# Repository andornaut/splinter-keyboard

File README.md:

# Splinter keyboard

A 62-key split columnar ergonomic keyboard.

**Status:** v4 PCB and case built and confirmed working with the [Splinter firmware](https://github.com/andornaut/qmk_firmware/tree/splinter/keyboards/splinter).

This repo holds the hardware design files; firmware lives in a [separate repo](https://github.com/andornaut/qmk_firmware/tree/splinter/keyboards/splinter). Design pipeline: Keyboard Layout Editor -> Ergogen -> KiCad -> fabrication -> Onshape -> OrcaSlicer -> QMK (see [Developing](#developing)).

Related notes: [3D printing](https://github.com/andornaut/til/blob/main/docs/3d-printing.md), [electronics](https://github.com/andornaut/til/blob/main/docs/electronics.md), [keyboards](https://github.com/andornaut/til/blob/main/docs/keyboards.md).

## Versions

| Version    | MCU                                                                                                        | Changes from previous                                              | Firmware                                                                                         | Photo                                      |
| ---------- | ---------------------------------------------------------------------------------------------------------- | ------------------------------------------------------------------ | ------------------------------------------------------------------------------------------------ | ------------------------------------------ |
| [v4](./v4) | [splitkb Liatris](https://splitkb.com/products/liatris) (RP2040)                                           | Added USB VBUS detection and TRRS ESD protection                   | [splinter](https://github.com/andornaut/qmk_firmware/tree/splinter/keyboards/splinter)           | Pending                                    |
| [v3](./v3) | [Adafruit KB2040](https://www.adafruit.com/product/5302) (RP2040)                                          | Switched from AVR to RP2040                                        | [splinter-v3.0](https://github.com/andornaut/qmk_firmware/tree/splinter-v3.0/keyboards/splinter) |  |
| [v2](./v2) | [SparkFun Pro Micro](https://www.sparkfun.com/sparkfun-qwiic-pro-micro-usb-c-atmega32u4.html) (ATmega32U4) | Symmetrical enclosures; added a key (62 keys)                      | [splinter-2.0](https://github.com/andornaut/qmk_firmware/tree/splinter-2.0/keyboards/splinter)   |  |
| [v1](./v1) | [SparkFun Pro Micro](https://www.sparkfun.com/sparkfun-qwiic-pro-micro-usb-c-atmega32u4.html) (ATmega32U4) | Initial version: 61 keys, columnar layout, asymmetrical enclosures | [splinter-1.0](https://github.com/andornaut/qmk_firmware/tree/splinter-1.0/keyboards/splinter)   |  |

## Repository layout

Every version directory (`v1/` .. `v4/`) follows the same shape, though not every version has every part:

| Path                      | Contents                                                                                                                                                             |
| ------------------------- | -------------------------------------------------------------------------------------------------------------------------------------------------------------------- |
| `ergogen/config.yaml`     | Keyboard definition. The source of truth for everything downstream.                                                                                                  |
| `ergogen/footprints/`     | Symlink to the shared footprints below, so every version builds against one pinned set. Do not edit.                                                                 |
| `keyboard-layout-editor/` | Layout prototypes.                                                                                                                                                   |
| `kicad/unrouted/`         | Working boards. Ergogen generates into these; you route here.                                                                                                        |
| `kicad/routed/`           | Routed masters. The fab source.                                                                                                                                      |
| `kicad/unrouted-backups/` | Timestamped copies of the `unrouted/` boards, taken each time fresh ones overwrite them. Gitignored, and only the last few per board are kept.                       |
| `kicad/jlcpcb-parts.json` | LCSC part numbers, kept outside the `.kicad_pcb` so they survive regeneration. v4 only, and what makes assembly files appear.                                        |
| `onshape/`                | Case design and its exported STEP. v4 adds the build sheet, the rationale, and a script that builds the same design as geometry and validates the export against it. |
| `orcaslicer/`             | Slicer projects. v2 and v3 only.                                                                                                                                     |

Shared across versions:

| Path       | Contents                                |
| ---------- | --------------------------------------- |
| `ergogen/` | Footprints and helpers.                 |
| `scripts/` | Build steps.                            |
| `dist/`    | Build output. Generated, not committed. |

A `_` prefix on a PCB filename excludes it from every step.

## Installation

| Tool                                                      | Needed for                                                                                     |
| --------------------------------------------------------- | ---------------------------------------------------------------------------------------------- |
| [KiCad 10](https://www.kicad.org)                         | Routing, and `kicad-cli` for gerber export and headless DRC                                    |
| [Node.js](https://nodejs.org/en)                          | Ergogen and the npm scripts                                                                    |
| [Python 3](https://www.python.org)                        | The build steps (stdlib only; `pcbnew` comes from KiCad)                                       |
| [OrcaSlicer](https://github.com/OrcaSlicer/OrcaSlicer)    | Slicing the printed case                                                                       |
| [FreeCAD](https://www.freecad.org)                        | `freecadcmd`, for [validating the case export](#step-6-onshape)                                |
| [Freerouting](https://github.com/freerouting/freerouting) | Optional, for [autorouting](#autorouting-optional)                                             |
| [KiKit](https://github.com/yaqwsx/KiKit)                  | Optional, for [panelization](#panelization-optional-for-pcba-cost); needs the git-master build |

```bash
# Include submodules when cloning
git clone --recursive git@github.com:andornaut/splinter-keyboard.git
cd splinter-keyboard

# Install the Node version from .nvmrc, then the deps (including Ergogen)
nvm install
npm install

# Install KiCad 10 (provides kicad-cli, used for fab file generation)
sudo add-apt-repository ppa:kicad/kicad-10.0-releases
sudo apt install kicad

# Fallback only if you cloned without --recursive
git submodule update --init --recursive
```

OrcaSlicer, FreeCAD, KiCad, Freerouting and KiKit also install from [these Ansible tasks](https://github.com/andornaut/ansible-ctrl/blob/main/roles/hobbies/tasks/main.yml) (tags `orcaslicer`, `freecad` and `kicad`; Freerouting and KiKit come with `kicad`).

**Updating footprint submodules.** `npm run ergogen` uses `ceoloide` and `infused-kim` at their pinned revision and never advances them, so builds stay reproducible. To re-pin:

```bash
git submodule update --remote ergogen/footprints/ceoloide ergogen/footprints/infused-kim
git add ergogen/footprints/ceoloide ergogen/footprints/infused-kim
git commit -m "Bump footprint submodules"
```

## Commands

Run everything through `npm run` from the repo root: the scripts read the active version from `config.VERSION` in [`package.json`](./package.json).

| Command                                                                            | Does                                                                                       |
| ---------------------------------------------------------------------------------- | ------------------------------------------------------------------------------------------ |
| `pipeline`                                                                         | The full build, every gate in order. The normal entry point. Add `-- -v` for the full log. |
| `ergogen`                                                                          | Generate outlines and PCBs into `dist/${VERSION}/ergogen/`                                 |
| `watch` / `watch:sync-unrouted`                                                    | Re-run `ergogen` on every `config.yaml` change, the second also copying into `unrouted/`   |
| `copy:dist-to-unrouted`                                                            | `dist/` -> `unrouted/` (backs the old boards up to `unrouted-backups/` first)              |
| `copy:traces-to-unrouted`                                                          | Traces and teardrops from `routed/` back into `unrouted/`                                  |
| `copy:unrouted-to-routed`                                                          | `unrouted/` -> `routed/` (see [Saving to routed/](#saving-to-routed))                      |
| `fab`                                                                              | Gerbers, drill, and assembly BOM/CPL via `kicad-cli`                                       |
| `panelize`                                                                         | Combine both halves into one JLCPCB panel (optional)                                       |
| `route`                                                                            | Autoroute `unrouted/` via Freerouting (optional)                                           |
| `validate:provenance` / `validate:symmetry` / `validate:firmware` / `validate:fab` | The four gates (see [Validation](#validation))                                             |
| `clean`                                                                            | Remove `dist/`                                                                             |
| `lint` / `format`                                                                  | Prettier and ESLint, checking or fixing. `lint` is a CI gate                               |

## Developing

### Step 1. Configure

Set `config.VERSION` in [`package.json`](./package.json) to `v1`, `v2`, `v3`, or `v4`, by editing the file or with `npm pkg set config.VERSION=v4`.

### Step 2. [Keyboard Layout Editor](https://www.keyboard-layout-editor.com/)

Prototype a layout, export it to [`keyboard-layout-editor.json`](./v4/keyboard-layout-editor/keyboard-layout-editor.json) so you can re-import and iterate, then use it as the basis for the Ergogen design. To load it into the **Raw data** tab, paste it without its outer `[` and `]`: the tab takes the layout's rows directly, while the downloaded JSON wraps them in an array.

### Step 3. [Ergogen](https://github.com/ergogen/ergogen)

1. `docker compose up` starts the Ergogen GUI (it builds on first run); open <http://ergogen.internal> (needs [docker_etc_hosts](https://github.com/andornaut/docker_etc_hosts) for the `/etc/hosts` entry).
1. Paste in, edit, then download [`ergogen/config.yaml`](./v4/ergogen/config.yaml).
1. `npm run ergogen`, then `npm run copy:dist-to-unrouted`. Or just `npm run watch:sync-unrouted`.

- The GUI renders no PCBs and is client-side only. Edit there, copy back to `config.yaml` (the source of truth), build with `npm run ergogen`.
- The browser cannot load footprints from disk, so the [`Dockerfile`](./Dockerfile) bakes this repo's [custom footprints](./ergogen/footprints/) into the GUI image. An unregistered `what:` shows up as unknown; after adding one, `docker compose build --no-cache`.

### Step 4. [KiCad](https://www.kicad.org/)

Open a board from [`kicad/unrouted/`](./v4/kicad/unrouted/) and route it. Before saving:

- **Add teardrops** (Edit > Edit Teardrops, nothing selected for board-wide): stronger pad and via joints. Re-run after any reroute.
- **Run DRC** (Inspect > Design Rules Checker, "Refill all zones" checked): clear every violation and unrouted net. `npm run fab` re-runs it headlessly, but fixing it here beats reading the JSON.
- **Check copper and silk** visually: no isolated GND islands or stranded pads; silk clear of pads and the board edge.

After regenerating with Ergogen, `npm run copy:traces-to-unrouted` brings the traces and teardrops from `routed/` back into `unrouted/` (then File > Revert in KiCad).

#### Saving to routed/

`npm run copy:unrouted-to-routed` writes the masters' `.kicad_pro` and `.kicad_dru` first, since the stages that move copper measure against the clearances those hold. Then, one master at a time, it copies the working board onto its master in [`kicad/routed/`](./v4/kicad/routed/) and runs:

| Stage        | What it does                                                                                                                 |
| ------------ | ---------------------------------------------------------------------------------------------------------------------------- |
| GND pour     | Floods a ground plane on whichever side costs less (scored per board, F.Cu vs B.Cu)                                          |
| Cleanup      | Strips copper no route uses: dangling tracks and the vias they strand, tracks buried in pads, redundant vias, split segments |
| Pattern snap | Pulls strays onto the repeated shape they belong to, within a per-endpoint cap                                               |
| Sliver tidy  | Collapses any segment left shorter than it is wide, within a per-endpoint cap                                                |

One master at a time, copy included, because any stage can stop the build: a master this run has not reached yet is still the routed board it was, rather than an un-poured working copy that nothing downstream would catch.

The last three stages feed each other: a collapsed sliver can leave a run the next snap recognises, and a snap leaves fragments for the next cleanup to merge and can leave a sliver of its own. So they repeat until a pass changes nothing, and a board still changing on the last allowed pass stops the build instead of shipping a master its own tooling has not finished with.

The working boards keep the stripped copper, mainly the footprints' unused `include_traces_vias` stubs, since a later reroute may pick it up.

Pattern snap and sliver tidy move copper rather than only removing it, so both are capped and neither guesses: pattern snap reports a stray it may not move and leaves it, while sliver tidy stops the build:

- **Pattern snap.** The matrix is a grid, so most of the routing is one motif repeated, and hand-drawn copies land a fraction of a millimetre apart. DRC never sees it, because each copy is individually legal. Anything beyond the cap is a routing decision rather than a stray, so it is reported and left alone.
- **Sliver tidy.** Moving one end of a run pivots the whole run, so a collapse is refused if it exceeds the cap or would swing copper into another net's clearance or a keepout. The refusal names the sliver and the reason; close it in KiCad by dragging the two runs together, or by re-routing clear of the named area.

#### Autorouting (optional)

KiCad has no built-in autorouter. `npm run route` routes the [`unrouted/`](./v4/kicad/unrouted/) boards in place via [Freerouting](https://github.com/freerouting/freerouting), leaving `routed/` untouched; expect to hand-clean the result, then File > Revert. Raising via cost trades vias for _unrouted nets_, so it cannot beat hand-routing on via count.

| Env var                          | Default     | Values                                                |
| -------------------------------- | ----------- | ----------------------------------------------------- |
| `FREEROUTING_PASSES`             | 100         |                                                       |
| `FREEROUTING_STRATEGY`           | greedy      | greedy, global, hybrid                                |
| `FREEROUTING_SELECTION`          | prioritized | prioritized, random, sequential                       |
| `FREEROUTING_VIA_COST`           | 50          | higher = fewer vias                                   |
| `FREEROUTING_UNDESIRED_DIR_COST` | unset       | cost of routing against a layer's preferred direction |
| `FREEROUTING_LOG_LEVEL`          | WARN        | ERROR, WARN, INFO, DEBUG, TRACE                       |

### Step 5. Fabrication (JLCPCB)

`npm run fab` exports from `routed/` into `dist/${VERSION}/kicad/jlcpcb/<name>/`:

| Output                             | Contents                                                                                                                                                                                         |
| ---------------------------------- | ------------------------------------------------------------------------------------------------------------------------------------------------------------------------------------------------ |
| `<name>-gerber.zip`                | Gerbers and drill: the bare PCB                                                                                                                                                                  |
| `<name>-BOM.csv`, `<name>-CPL.csv` | Assembly files, written only when [`jlcpcb-parts.json`](./v4/kicad/jlcpcb-parts.json) is present                                                                                                 |
| `<name>-drc.json`                  | Headless DRC report, written per board before that board's export. Any error-level violation or unrouted net stops the run there, so a failing board never overwrites its own last-good gerbers. |

A provenance check gates the whole run before any board is touched, so a master that drifted from `config.yaml` produces nothing at all.

Which parts JLCPCB places and which you hand-solder is version-specific; see the [v4 notes](./v4/README.md#fabrication-jlcpcb).

**Ordering** from [JLCPCB](https://jlcpcb.com/): upload each `<name>-gerber.zip`, plus the matching BOM and CPL for assembly. Check placement in the [DFM viewer](https://cart.jlcpcb.com/quote/gerberviewThree); fix a mis-oriented part via its `rotation` in [`jlcpcb-parts.json`](./v4/kicad/jlcpcb-parts.json) and re-run.

#### Panelization (optional, for PCBA cost)

`npm run panelize` combines `left` and `right` into one panel so JLCPCB's per-order assembly setup and stencil fees are paid once instead of twice. **The panel is not orderable yet:** its frame is not tabbed to the boards, and its fiducials sit on its tooling holes at the rail's inner edge. Order the halves separately until `scripts/panelize.py` is fixed. Outputs to `dist/${VERSION}/kicad/jlcpcb/panel/`; the per-half `fab` remains the strict DRC gate. Requires [KiKit](https://github.com/yaqwsx/KiKit) (git-master build for KiCad 10); point it at an interpreter with `KIKIT_PYTHON`.

### Step 6. [Onshape](https://cad.onshape.com)

1. Create a document and start a sketch.
1. Select "Insert a DXF or DWG file" > "Import ..." (bottom of the dialog) > `dist/${VERSION}/ergogen/outlines/full_unfilleted.dxf`. That is the nominal hull rather than the fabricated edge: the fillet only removes material, so a pocket cut to the hull can never come out undersized.
1. Design the case to [`onshape/BUILD.md`](./v4/onshape/BUILD.md), which carries every dimension and the feature-by-feature recipe, then export it to `dist/${VERSION}/onshape/`.
1. Validate both halves against the reference, `FC_HALF=left FC_COMPARE=dist/${VERSION}/onshape/<export>.step freecadcmd v4/onshape/gen-case.py` and again with `FC_HALF=right`, and decide every difference it reports: move the model to the reference, record it in `v4/onshape/differences.json` as intentional, or fix it as an error. See [Validating your model](./v4/onshape/BUILD.md#validating-your-model).
1. Once both halves validate, copy the export over `v4/onshape/Splinter keyboard v4 - Filament.step`. Validate the aluminium configuration's export the same way with `FC_VARIANT=aluminium` added, then copy it over `Splinter keyboard v4 - Aluminium.step`.
1. Export the aluminium configuration again one part per file, validate each half's pair with `FC_VARIANT=aluminium FC_COMPARE=<shell>.step,<plate>.step`, and copy them over `v4/onshape/Splinter keyboard v4 - Aluminium - {Left,Right} {shell,plate}.step`.

### Step 7. [OrcaSlicer](https://github.com/OrcaSlicer/OrcaSlicer)

1. Open or create a project and import [`Splinter keyboard v4 - Filament.step`](./v4/onshape/Splinter%20keyboard%20v4%20-%20Filament.step).
1. Slice and print the case.
1. Install an [M2.5 heat-set insert](https://cnckitchen.store/products/gewindeeinsatz-threaded-insert-m2-5-standard-100-stk-pcs) into each mounting boss with a soldering iron, then clamp the PCB with the [M2.5 screws](./v4/README.md#bill-of-materials-bom).

#### Alternative: machined aluminium case (JLCCNC)

Upload the model's aluminium configuration (tapped holes, see [Aluminium variant](./v4/onshape/BUILD.md#aluminium-variant)) to [JLCCNC](https://jlccnc.com) as four files, one part each, since JLCCNC quotes per file: [`Splinter keyboard v4 - Aluminium - Left shell.step`](./v4/onshape/Splinter%20keyboard%20v4%20-%20Aluminium%20-%20Left%20shell.step), [`Splinter keyboard v4 - Aluminium - Left plate.step`](./v4/onshape/Splinter%20keyboard%20v4%20-%20Aluminium%20-%20Left%20plate.step), [`Splinter keyboard v4 - Aluminium - Right shell.step`](./v4/onshape/Splinter%20keyboard%20v4%20-%20Aluminium%20-%20Right%20shell.step) and [`Splinter keyboard v4 - Aluminium - Right plate.step`](./v4/onshape/Splinter%20keyboard%20v4%20-%20Aluminium%20-%20Right%20plate.step). Attach each part's drawing to that part, and quote each part once:

| Setting        | Value                                                                                                                                                                                                                                                                                                                                                                                                                                                                                                                                                                                                                                                                                                                                                                                |
| -------------- | ------------------------------------------------------------------------------------------------------------------------------------------------------------------------------------------------------------------------------------------------------------------------------------------------------------------------------------------------------------------------------------------------------------------------------------------------------------------------------------------------------------------------------------------------------------------------------------------------------------------------------------------------------------------------------------------------------------------------------------------------------------------------------------ |
| Material       | 6061 aluminium (JLCCNC's standard alloy)                                                                                                                                                                                                                                                                                                                                                                                                                                                                                                                                                                                                                                                                                                                                             |
| Surface finish | Bead blasting + anodizing, dark grey. Order all four parts together so they anodize in one batch and match                                                                                                                                                                                                                                                                                                                                                                                                                                                                                                                                                                                                                                                                           |
| Tolerance      | Select +-0.1 on all four parts, and mark the mating dimensions +-0.1 on each part's drawing: JLCCNC applies a selected tolerance only to dimensions annotated on the 2D drawing, and everything else defaults to ISO 2768 medium (+-0.5 above 120mm, more than the plate's 0.40 total clearance in its cavity). The drawings dimension between straight edges: the shell cavity 161.00 wide and 102.25 tall at its outer side, the plate 160.60 and 101.85. Holes are placed from mating edges, listed outer / centre / inner hole. The shells: from the cavity's outer side (38.13, 77.18, 114.33), and from the cavity edge opposite the thumb (63.65, 37.83, 59.95). The plates: from the plate's outer side (37.93, 76.98, 114.13) and its thumb-side edge (38.40, 64.23, 42.10) |
| Threaded holes | Threads YES on each shell: 3 x M2.5x0.45. Threads NO on the plates. Attach every part's PDF by hand: the PDFs are not named like the STEPs. The heat-set inserts are for the printed case only                                                                                                                                                                                                                                                                                                                                                                                                                                                                                                                                                                                       |
| Order remarks  | Shells: "Threads: 3 x M2.5x0.45 blind, 2.05 drill 4.00 deep, full thread to 2.65 required (screw reaches 2.53). If you can't hold 2.65, contact me before machining." Plates: "Fits into the matching shell's cavity with 0.20/side clearance; its three 2.90 holes must line up with the shell's tapped holes."                                                                                                                                                                                                                                                                                                                                                                                                                                                                     |
| Edges          | JLCCNC breaks external edges by about 0.2 by default. The drawings' title block says only "REMOVE BURRS", so that default applies to the switch recess rims too, which the model leaves square                                                                                                                                                                                                                                                                                                                                                                                                                                                                                                                                                                                       |

A STEP file cannot carry threads, so model each hole at the ~2.05mm tap-drill diameter and upload a PDF with an `M2.5x0.45` callout, 4.00 drill and full thread to 2.65: the drill leaves 1.35 of run-out below the full thread, more than half the diameter, so a standard tap reaches it. Every hole shares the thread spec and the depth, so one callout covers all three; take both from the [build sheet](./v4/onshape/BUILD.md#screw-bosses). [`Splinter v4 left shell.pdf`](./v4/onshape/Splinter%20v4%20left%20shell.pdf) and [`Splinter v4 right shell.pdf`](./v4/onshape/Splinter%20v4%20right%20shell.pdf) carry the thread callouts and the +-0.1 annotations above; [`Splinter v4 left plate.pdf`](./v4/onshape/Splinter%20v4%20left%20plate.pdf) and [`Splinter v4 right plate.pdf`](./v4/onshape/Splinter%20v4%20right%20plate.pdf) carry the annotations only. To redraw one, make an Onshape Drawing of the Aluminium configuration and use its **Hole callout** tool on a tapped hole's edge; it reads the spec from the Hole feature.

### Step 8. [QMK firmware](https://qmk.fm/)

Install the [custom QMK firmware](https://github.com/andornaut/qmk_firmware/tree/splinter/keyboards/splinter).

## Automation

### One-command pipeline

`npm run pipeline` re-syncs already-routed boards after a config change:

| #   | Step                      | Does                                                  |
| --- | ------------------------- | ----------------------------------------------------- |
| 1   | `ergogen`                 | Rebuild the boards from `config.yaml`                 |
| 2   | `copy:dist-to-unrouted`   | Fresh boards into `unrouted/`, old ones backed up     |
| 3   | `copy:traces-to-unrouted` | Replay the masters' routing onto them                 |
| 4   | `copy:unrouted-to-routed` | Save back to `routed/` ([details](#saving-to-routed)) |
| 5   | `validate:provenance`     | Stamps match `config.yaml`                            |
| 6   | `validate:symmetry`       | The halves are exact mirror images                    |
| 7   | `validate:firmware`       | Boards match the QMK matrix                           |
| 8   | `fab`                     | Export gerbers and assembly files                     |
| 9   | `validate:fab`            | Audit those outputs                                   |

Every step is a hard gate. `panelize` runs last and is the only optional one, skipped with a note when KiKit is absent.

A step reports what it changed and what wants reading; lines that only confirm nothing needed doing are held back, since each step's closing `OK:` line already carries the count they would have added up to. `npm run pipeline -- -v` shows them all, plus Ergogen's own narration and the artifact listing file by file.

**It requires existing routed masters** and does not route for you: step 3 replays their traces onto the fresh boards and aborts if a master carries no human routing. For a first route, or when geometry moves enough that the old traces no longer fit, route by hand in KiCad (Step 4).

### Validation

| Gate                  | Checks                                                                                                                                                                                                                                                                            |
| --------------------- | --------------------------------------------------------------------------------------------------------------------------------------------------------------------------------------------------------------------------------------------------------------------------------- |
| `validate:provenance` | Every board's stamp still matches `config.yaml`, and the boards in a stage were all built in the same run, so neither a stale master nor a half restored on its own can reach fab                                                                                                 |
| `validate:symmetry`   | The two halves are exact mirror images: outline, parts, pads, rule areas and silk, compared in each board's own frame so the per-board recentering is not read as asymmetry                                                                                                       |
| `validate:firmware`   | Both halves wire the MCU header identically, and the matrix they imply equals the QMK `keyboard.json`                                                                                                                                                                             |
| `validate:fab`        | The exported artifacts: a board-spanning GND plane on both master and gerbers, a complete gerber set, a non-empty BOM and CPL with every assembled footprint appearing in the CPL exactly once, outputs no older than their sources, comparable teardrop counts across the halves |

`validate:fab` also warns, without failing, when a master was built from an uncommitted tree: the board is fine, but its recorded commit means nothing, so the warning is expected during ordinary in-progress work.

`validate:symmetry` holds the halves to being exact mirrors of each other. The licensed exception is the keys of the outer pinky columns, which differ by design (the left pinky is 1.5u; the right is 1u plus an extra inner column). Drift here is otherwise invisible: both halves still route, pass DRC, fab and assemble, and it surfaces only as a case that fits one half and rocks on the other, or a clearance that is comfortable on one half and marginal on the other. Both halves are generated from one set of mirrored anchors in `config.yaml`, so a failure is a config change to undo rather than a board to edit.

Four kinds of part are placed in the same orientation on both halves rather than mirrored, because the parts themselves cannot be: an MX switch and its Kailh socket have an asymmetric pin pattern, the matrix diode wires straight to a switch pin and follows it, the MCU is a module that plugs in one way up, and the TRRS jack mounts on the back of both halves with the same pin pattern. Their pads therefore land at mirrored positions carrying the opposite pin at each. Key _placements_ still mirror exactly, and so does every clearance measured from key geometry; only pad-to-edge distances within a key differ between the halves. Hand routing is not compared at all.

`validate:firmware` reads the `keyboard.json` at `config.FIRMWARE` in [`package.json`](./package.json), which ships as a path to a sibling `qmk_firmware` checkout so the check covers what you are about to flash rather than what is pushed. Without that checkout the step fails and no gerbers are produced; pass `--firmware <url|path>` or set `$SPLINTER_FIRMWARE_JSON` instead.

### Provenance stamp

The copy steps and manual routing let `routed/` drift from `config.yaml`, so you could fab a stale board. `npm run ergogen` stamps each board with a hash of `config.yaml`; `fab` refuses a drifted or unstamped master, and `validate:provenance` checks without fabbing. Clear a mismatch by re-running the pipeline, re-routing if needed.

Restoring or rebuilding one half on its own is invisible to the hash, since identical config bytes hash the same across builds, so `validate:provenance` also requires every board in a stage to carry the same stamp. The two stages are compared separately: `unrouted/` is expected to be newer than `routed/` between an `ergogen` run and the save back to the masters.

A panel inherits its masters' stamp rather than getting one of its own, so its `commit=` names the commit the panelled copper came from. Masters whose stamps disagree stop `panelize`, since a panel merged from two generations of board has no single provenance to report.

Only `config.yaml` is hashed, so a footprint `.js` or Ergogen-version change can move geometry without tripping the check, while a comment-only config edit trips a false "stale".

### Reproducing a previous build

A stamp names the commit the build's _inputs_ came from, never the commit that contains the stamped board: the stamp is written into the board, so it can only name its own parent. To get the boards a stamp describes, check that commit out and rebuild.

```bash
git checkout <the commit= from the stamp>
npm run pipeline
```

Taking `kicad/routed/*.kicad_pcb` straight from that commit instead gives you the _previous_ build's masters. Rebuilding reproduces copper, drill, mask, paste, outline and the assembly files identically; only the `built=` timestamp drawn on the silk and a few microns of teardrop fill tessellation differ.

## Verification

Run `make check` for containerized lint and committed-board provenance validation.
The checks do not regenerate, route or modify boards.

Native npm commands run locally. `npm run lint` checks formatting and JavaScript;
`npm run validate:provenance` validates committed boards. `npm run format` and the
commit hook preserve automatic formatting fixes.

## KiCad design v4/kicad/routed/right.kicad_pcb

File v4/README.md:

# Version 4 of the Splinter keyboard

A 62-key split columnar ergonomic keyboard with symmetrical enclosures and non-traditional backspace and backslash placement.

**Status:** PCB and case built and confirmed working.

- [QMK firmware](https://github.com/andornaut/qmk_firmware/tree/splinter/keyboards/splinter)
- Build and fabrication workflow: [root README](../README.md#developing)

Each PCB half:

| Outline                                      | Width     | Height    |
| -------------------------------------------- | --------- | --------- |
| Un-filleted hull                             | 160.00 mm | 119.00 mm |
| As fabricated, after the 1.5mm corner fillet | 160.00 mm | 118.59 mm |

The fillet rounds the corners off the height; the straight side edges hold the width. See the [case design notes](./onshape/README.md).

## Changes from v3

| Change                                                                                                                                         | Details                                    |
| ---------------------------------------------------------------------------------------------------------------------------------------------- | ------------------------------------------ |
| The [splitkb Liatris](https://splitkb.com/products/liatris) (RP2040) replaces the [Adafruit KB2040](https://www.adafruit.com/product/5302) MCU | [Microcontroller](#microcontroller)        |
| A TVS diode protects the TRRS serial line from ESD, and each jack contact has its own pad                                                      | [Split connection](#split-connection-trrs) |

## Microcontroller

The [splitkb Liatris](https://splitkb.com/products/liatris) wires its USB VBUS line to GP19, so QMK senses USB presence via `USB_VBUS_PIN` instead of the `SPLIT_USB_DETECT` polling loop. That removes the roughly two-second unresponsive window at boot and makes the board more reliable after KVM switches.

The MCU is socketed rather than soldered: each one sits in a pair of Mill-Max 12-pin sockets (see the [BOM](#bill-of-materials-bom)) so it can be removed and reused. It mounts on the bottom of the board, the same side as the diodes, hotswap sockets and the rest of the SMD parts, with its own components facing away from the board so its Boot button stays reachable. That seating determines which header column each matrix net lands on, so it is not interchangeable with the opposite orientation.

The matching firmware config (the `USB_VBUS_PIN` define and the `development_board` and split settings) lives in the [firmware repo](https://github.com/andornaut/qmk_firmware/tree/splinter/keyboards/splinter).

### Pinout

- [splitkb Liatris pinout](https://docs.splitkb.com/product-guides/liatris/pinout)
- [Custom Ergogen footprint: `mcu_liatris`](../ergogen/footprints/mcu_liatris.js), based on [ceoloide/mcu_nice_nano](../ergogen/footprints/ceoloide/mcu_nice_nano.js) and the [marbastlib KiCad footprint](https://github.com/ebastler/marbastlib)

| Left     |     |     | Right      |
| -------- | --- | --- | ---------- |
| P1 (GP0) |     |     | RAW        |
| P0 (GP1) |     |     | GND        |
| GND      |     |     | RST        |
| GND      |     |     | VCC        |
| P2 (GP2) |     |     | P21 (GP29) |
| P3 (GP3) |     |     | P20 (GP28) |
| P4 (GP4) |     |     | P19 (GP27) |
| P5 (GP5) |     |     | P18 (GP26) |
| P6 (GP6) |     |     | P15 (GP22) |
| P7 (GP7) |     |     | P14 (GP20) |
| P8 (GP8) |     |     | P16 (GP23) |
| P9 (GP9) |     |     | P10 (GP21) |

The Liatris also carries five extra bottom pins (GP12 to GP16) that the footprint can place but the matrix does not use.

GP19, the `USB_VBUS_PIN`, is the Liatris's internal VBUS-sense pin rather than a header net, so it is absent from the table. The `P19` row maps to GP27, a separate matrix pin.

Which column is which is set by one parameter, `raw_pin_column` on the [`mcu_liatris`](../ergogen/footprints/mcu_liatris.js) footprint: `front_left` or `front_right`, named from the PCB front. [ergogen/config.yaml](./ergogen/config.yaml) sets it explicitly to `front_right`, the footprint's default. From the back, where the MCU mounts, the columns read the other way round. The table above is `front_right`, the datasheet arrangement. Both halves must share the value, because the Liatris cannot be mirrored.

To check it on a physical board, seat the module and confirm its RAW pin lands on the pad silkscreened RAW. The board silk and the config net names cannot tell you: they move together when the parameter flips.

### Verifying the pin mapping

A board whose matrix nets reach the wrong MCU column is fully routed, shorts nothing, and passes DRC and every other check here. It fails only once an MCU is plugged in, which is after the boards are paid for. `npm run validate:firmware` is the gate for that, and both of its checks are required:

- **Half symmetry.** Both halves must wire the MCU header identically. Halves that disagree mean one of them is backwards.
- **Firmware agreement.** The matrix pins implied by the boards must equal the QMK [keyboard.json](https://github.com/andornaut/qmk_firmware/blob/splinter/keyboards/splinter/keyboard.json), both halves plus the serial pin.

What the checks guarantee is that the two halves agree and that the config's net assignments never silently drift from the firmware's pin arrays. What they cannot prove is that the mapping matches physical reality: both mirrorings of the header produce electrically valid boards, the footprint's silk pin labels are generated from the same table as the pad nets, and the firmware check compares net names through that same table. All three move together under a `raw_pin_column` flip.

Only hardware settles that, and it is settled: the current value, `front_right`, is confirmed on an assembled and working board. Treat it as fixed. Changing it, or changing how the MCU seats, invalidates that confirmation and needs a fresh check on hardware.

## Split connection (TRRS)

A TRRS cable joins two HCTL HC-PJ-320A-4P-D jacks. The half with USB is the primary; it powers the other half over the cable and talks to it on one half-duplex serial line.

**Never plug or unplug the TRRS cable while either half has USB.** Unplug USB first; connect the TRRS cable before USB.

### Pinout

| Plug contact | Jack pad | Net | Liatris pin | Carries                       |
| ------------ | -------- | --- | ----------- | ----------------------------- |
| Tip          | T        | VCC | VCC         | 3.6V supply to the other half |
| Ring 1       | R1       | -   | -           | nothing                       |
| Ring 2       | R2       | P2  | GP2         | half-duplex serial data       |
| Sleeve       | S        | GND | GND         | common ground                 |

The jack footprint, [`trrs_hc_pj320a`](../ergogen/footprints/trrs_hc_pj320a.js), follows HCTL's recommended layout and names each pad for the plug contact it reaches. Both halves mount the jack on the back, so both use the same pin pattern.

### Data path, each half

```text
jack R2 --(P2)--+-- Liatris GP2
                |
               TVS
                |
               GND
```

| Part            | Specification                                                                  | Function                       |
| --------------- | ------------------------------------------------------------------------------ | ------------------------------ |
| TVS             | Littelfuse SMF5.0CA (C1851363), bidirectional, 5V standoff, 6.4V breakdown min | Clamps ESD and cable discharge |
| Series resistor | None                                                                           | See below                      |

### Decisions

| Decision                                     | Rationale                                                                                                                                                                                                                                                                                                                                                                                                                                                                                                                                                                                                 |
| -------------------------------------------- | --------------------------------------------------------------------------------------------------------------------------------------------------------------------------------------------------------------------------------------------------------------------------------------------------------------------------------------------------------------------------------------------------------------------------------------------------------------------------------------------------------------------------------------------------------------------------------------------------------- |
| No series resistance on the data line        | QMK's RP2040 half-duplex driver has the receiving half drive the line high (2mA setting) while the sender pulls it low (12mA), so the receiver reads a divider and series resistance lifts the low it sees. With nothing in series the low is about 0.36V against a 0.8V input-low limit; 100Ω per half lifts it well above that limit and the link fails.                                                                                                                                                                                                                                                |
| Bidirectional TVS with a 5V standoff         | It conducts only above 6.4V, so never on the 3.6V line in either polarity. It absorbs ESD energy; the RP2040's own clamp diodes conduct from about 4.1V. Its capacitance, about 1nF per half, settles within a small fraction of a bit at the default 230400 baud because the receiver drives the line high actively.                                                                                                                                                                                                                                                                                     |
| Sleeve on GND                                | The sleeve is the largest exposed contact on a loose plug, so it is the one that must not be live.                                                                                                                                                                                                                                                                                                                                                                                                                                                                                                        |
| Ring 1 unconnected                           | Only the tip carries VCC. With ring 1 on VCC as well, two cable conductors meet at the far half's VCC, and a part-withdrawn plug bridges them from the near half's VCC spring to its sleeve (GND) spring: a direct short of the supply. With one VCC conductor no plug position closes that loop.                                                                                                                                                                                                                                                                                                         |
| Liatris VCC jumper set to 3.6V (both halves) | The [VCC pin](https://docs.splitkb.com/product-guides/liatris/pinout) outputs USB voltage (about 5V) by default. A momentary VCC-to-data contact would then exceed the RP2040's 4.1V pin limit (IOVDD + 0.5V). At 3.6V nothing on the cable is above the logic supply. **Both modules must be set:** splitkb describes the VCC pin as the split peripheral's voltage input, and at 3.6V it feeds that half's 3.6V logic supply, so if the half with USB is still at 5V, the cable puts about 5V on the other half's RP2040. After setting both, confirm the half without USB still runs as the secondary. |
| No hot-plugging                              | Each band of a 3.5mm plug slides across the jack's other springs on the way in and out, so no pinout avoids momentary contact between VCC, data and GND. The choices above reduce what that contact can do; they do not make hot-plugging safe.                                                                                                                                                                                                                                                                                                                                                           |
| Never pair with a symmetric-footprint board  | Boards built with the symmetric `ceoloide/trrs_pj320a` footprint carry VCC on the sleeve and GND on ring 2. On one cable with a board of this revision, the sleeve joins VCC to GND. Build and use both halves from the same revision.                                                                                                                                                                                                                                                                                                                                                                    |

Firmware: `split.serial.pin` is GP2 on both halves, using the vendor (PIO) driver in half-duplex mode; `USB_VBUS_PIN` (GP19) decides which half is primary.

## Copper keepout zones

`npm run ergogen` adds copper keepout rule areas to the generated boards. They ride the copy steps into `unrouted/` and `routed/` automatically. Do not hand-edit them.

| Zone                 | Excludes                              | Purpose                                                                                                                                                                                                                                                                                                                          |
| -------------------- | ------------------------------------- | -------------------------------------------------------------------------------------------------------------------------------------------------------------------------------------------------------------------------------------------------------------------------------------------------------------------------------- |
| Perimeter pour ring  | The GND pour                          | Keeps the plane off the whole board edge. A ring just inside the edge, sized to clear the case support-wall lip, bridged straight across the USB cutout.                                                                                                                                                                         |
| Perimeter route ring | Tracks, vias, conductive pads         | Same ring, minus a carved-out band above the TRRS: the case's top wall has the port opening there, so the TRRS top through-holes may reach the edge. The inner vertical edge stays full height, so copper under the side wall is still flagged.                                                                                  |
| Screw-boss disks     | Pour, tracks, vias                    | One disk per mounting hole, extending past the boss edge by the margin the script sets.                                                                                                                                                                                                                                          |
| Reset-switch area    | Pour, tracks, vias (back copper only) | The gap between each side's two reset-switch pads, which ALPS's SKQG land drawing marks as a prohibited area for copper tracks. A second, pour-only rectangle clears the GND pour from around the whole switch and its four pads; tracks stay allowed there, because the switch's own GND and RST traces run along its pad rows. |

Bare mechanical (NPTH) holes, meaning the mounting holes and the TRRS locating holes, carry no copper and are always allowed. The conductive-pad check is a custom DRC rule in each board's `<name>.kicad_dru`; it keys on pad type, so SMD lands like the hotswap sockets are caught too.

## Bill of materials (BOM)

| Description              | Quantity | Part                                                                                                                                                                                                                                 |
| ------------------------ | -------- | ------------------------------------------------------------------------------------------------------------------------------------------------------------------------------------------------------------------------------------ |
| Diodes                   | 62       | [1N4148W](https://www.lcsc.com/product-detail/C81598.html) (C81598, SOD-123 switching; JLCPCB Basic, alt Jingdao C115103, check stock)                                                                                               |
| Hot swap sockets         | 62       | [Adafruit 4958](https://www.digikey.ca/en/products/detail/adafruit-industries-llc/4958/13997772) (Kailh CPG151101S11 MX hotswap socket; DigiKey 1528-4958-ND, 20/pack)                                                               |
| Keycap set               | 1        | [GMK CYL Sixes keycaps](https://www.deskhero.ca/products/gmk-sixes-keycaps-extras) and [Ergo Kit](https://www.deskhero.ca/products/gmk-sixes-keycaps-extras?variant=40182207676482)                                                  |
| Key switches             | 62       | [Cherry MX Ergo Clear](https://shockport.ca/collections/switches-1/products/cherry-mx-ergo-clear)                                                                                                                                    |
| Microcontrollers         | 2        | [splitkb Liatris](https://splitkb.com/products/liatris) (RP2040). Set each module's VCC jumper to 3.6V before use, including a replacement module, which ships at 5V; see [Split connection](#split-connection-trrs)                 |
| Screws                   | 6        | M2.5x8 button head, ISO 7380 (one per boss, 3 per half). The counterbores put every head at one level, so one length serves all six; see the [case build sheet](./onshape/BUILD.md#screw-bosses)                                     |
| Silicone bumpers         | 8        | [10x2mm Silicone Rubber Bumpers](https://www.aliexpress.com/item/1005005315398342.html)                                                                                                                                              |
| Sockets (12-pin)         | 4        | [Mill-Max 315-43-112-41-003000](https://www.mouser.ca/ProductDetail/575-3154311241003000) ([series documentation](https://mm.digikey.com/Volume0/opasdata/d220001/medias/docus/2481/310%2C%20311%2C%20315%20Series%20%28in.%29.pdf)) |
| Socket pins              | 48       | [Mill-Max 3320-0-00-15-00-00-03-0](https://www.mouser.ca/ProductDetail/575-3320000150000030)                                                                                                                                         |
| Switches/buttons (reset) | 2        | [5.2mm SMD tact switch](https://www.lcsc.com/product-detail/C115351.html) (C115351, ALPS SKQGABE010; JLCPCB Extended, alt ALPS SKQGAFE010 C202424; placed by JLCPCB)                                                                 |
| Threaded inserts         | 6        | [M2.5 threaded inserts](https://cnckitchen.store/products/gewindeeinsatz-threaded-insert-m2-5-standard-100-stk-pcs) (one per boss, 3 per half; 3.6mm hole, bore depth in the [case build sheet](./onshape/BUILD.md#screw-bosses))    |
| TRRS cables              | 1        | [King Cables TRRS Cable](https://www.kingcables.org/)                                                                                                                                                                                |
| TRRS jacks               | 2        | [HCTL HC-PJ-320A-4P-D](https://www.lcsc.com/product-detail/Audio-Connector-Headphone_HCTL-HC-PJ-320A-4P-D_C5372851.html)                                                                                                             |
| TVS diodes               | 2        | [Littelfuse SMF5.0CA](https://www.lcsc.com/product-detail/C1851363.html) (C1851363, SOD-123FL bidirectional, 5V standoff; JLCPCB Extended; alt MDD C364279, TWGMC C726939)                                                           |

## Fabrication (JLCPCB)

See the root README's [fabrication step](../README.md#step-5-fabrication-jlcpcb) for how `npm run fab`, the DRC gate, and [jlcpcb-parts.json](./kicad/jlcpcb-parts.json) work. This section covers only what is v4-specific.

| Part                             | Assembly                                                                                                                                                                   |
| -------------------------------- | -------------------------------------------------------------------------------------------------------------------------------------------------------------------------- |
| Matrix diodes, TVS, reset switch | Placed by JLCPCB, Economic PCBA, bottom side. The TVS and the reset switch are Extended parts, so each adds a feeder-loading fee per order                                 |
| Hotswap sockets                  | Do-Not-Place. Keeping them off the assembly BOM is what holds the order on the cheaper **Economic** PCBA service: they are Standard-only and not stocked for JLC assembly. |
| MCU (Liatris), TRRS jack         | Do-Not-Place. The jack and the MCU's sockets are hand-soldered; the MCU plugs into the sockets                                                                             |

The LCSC and vendor links in the [BOM](#bill-of-materials-bom) for Do-Not-Place parts are for sourcing only.

The diode footprint (`diode_sod123`) carries `rotation: 180` in [jlcpcb-parts.json](./kicad/jlcpcb-parts.json): JLCPCB's own C81598 footprint already puts the cathode on pad 1, so the 180 is the bottom-side placement correction, and the band lands on pad 1, the cathode and row net. The TVS is bidirectional, so its rotation is irrelevant. The reset switch's footprint matches JLCPCB's at 0 degrees, and each of its pad rows is one terminal pair, so 0 and 180 are equivalent.

Order each half separately, with these settings:

| Setting       | Value                                                                                                  |
| ------------- | ------------------------------------------------------------------------------------------------------ |
| Files         | `<half>-gerber.zip`, then `<half>-BOM.csv` and `<half>-CPL.csv` from `dist/v4/kicad/jlcpcb/<half>/`    |
| PCB           | 2 layers, 1.6mm, Surface Finish: LeadFree HASL, Mark on PCB: Remove Mark, Confirm Production File: Yes |
| PCBA          | Economic, Assembly Side: Bottom, at least 2 assembled boards                                           |
| Tooling holes | Added by JLCPCB; check where they land when confirming the production file                             |
| Parts check   | three BOM lines: C81598 (30 left, 32 right), C1851363 x1, C115351 x1                                   |
| DFM viewer    | each diode band on its row-trace end, the TVS on its pads, B1's four terminals on their pads           |

The plated slots for the jack are 0.9 x 1.5mm, under JLCPCB's 2:1 slot ratio, so expect a DFM note; JLCPCB has fabricated the same slots before.

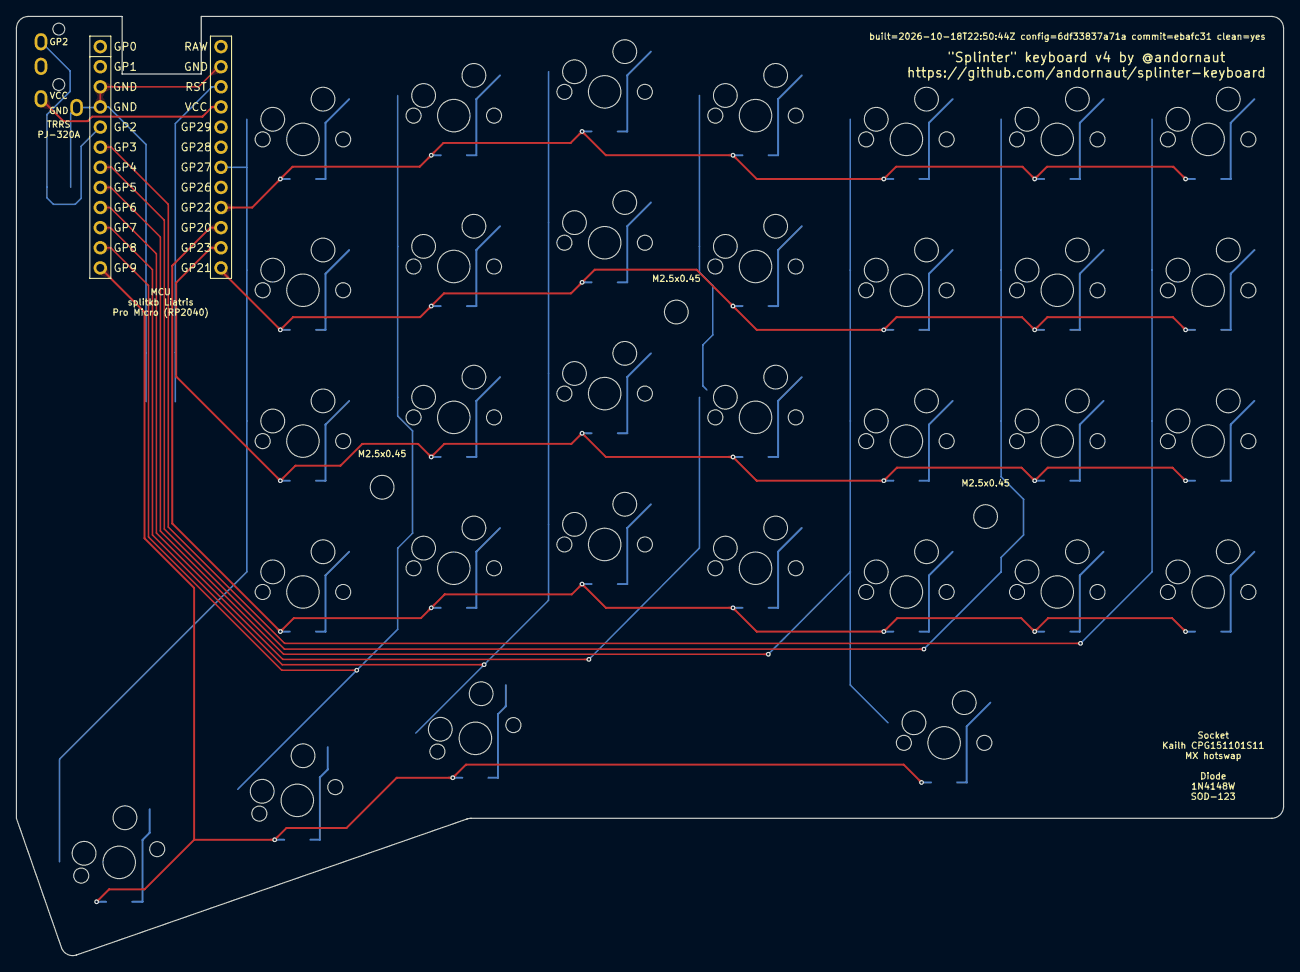
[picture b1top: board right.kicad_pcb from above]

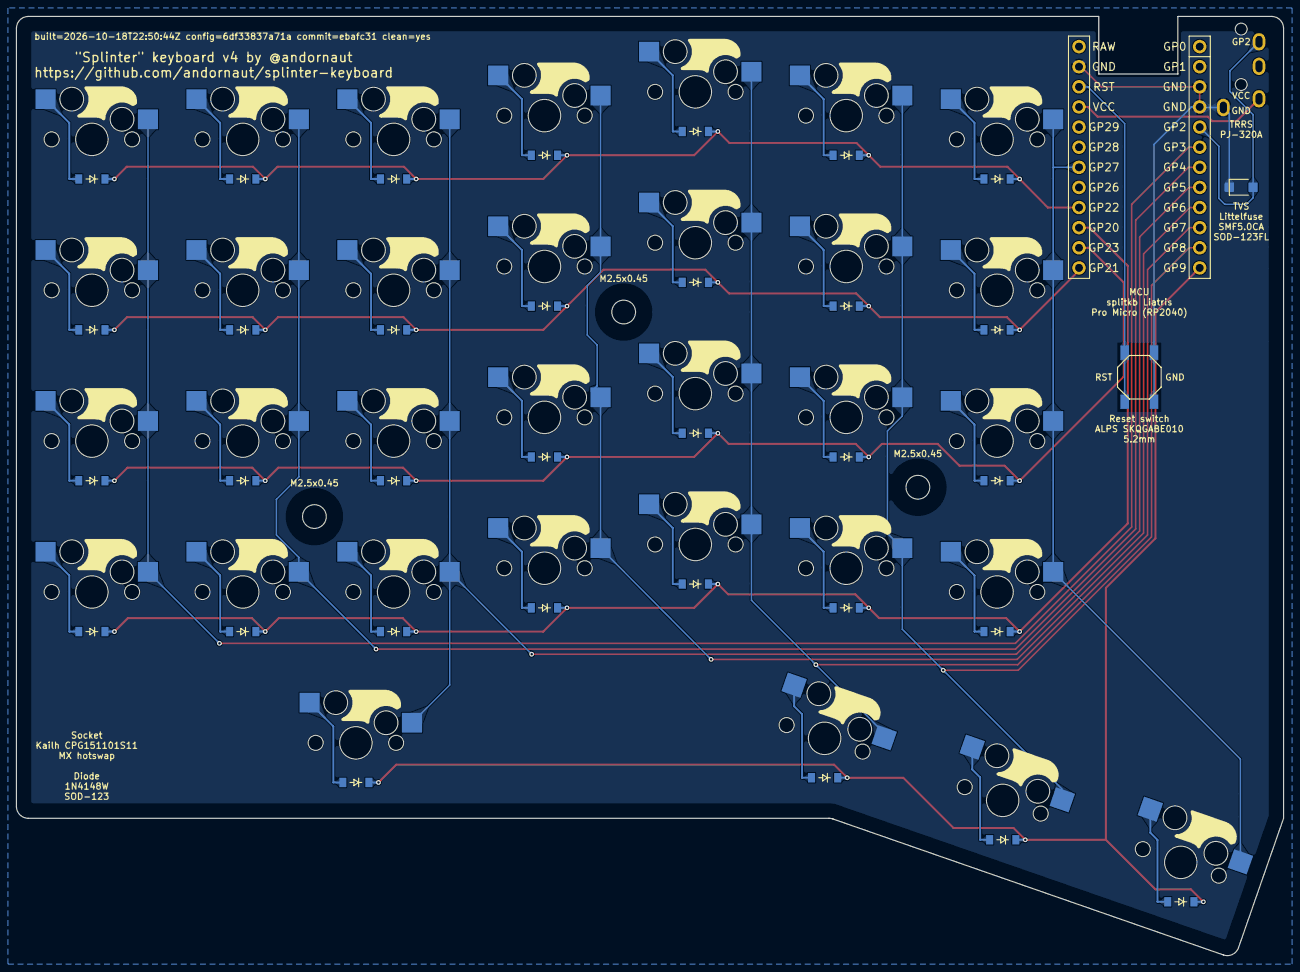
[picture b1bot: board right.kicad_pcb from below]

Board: 2 copper layers, 160.0 x 118.6 mm, 71 parts (68 on the bottom side), 48 nets.

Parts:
B1: SW_TACT_ALPS_SKQGABE010
D1, D2, D3, D4, D5, D6, D7, D8, D9, D10, D11, D12, D13, D14, D15, D16, D17, D18, D19, D20, D21, D22, D23, D24, D25, D26, D27, D28, D29, D30, D31, D32: diode_sod123
D33: SMF5.0CA; D_SOD-123FL
MCU1: mcu_liatris
MH1, MH2, MH3: mounting_hole_npth
S1, S2, S3, S4, S5, S6, S7, S8, S9, S10, S11, S12, S13, S14, S15, S16, S17, S18, S19, S20, S21, S22, S23, S24, S25, S26, S27, S28, S29, S30, S31, S32: switch_mx
TRRS1: trrs_hc_pj320a

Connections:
GND: B1.1, D33.K, MCU1.2, MCU1.21, MCU1.22, TRRS1.S
P2: D33.A, MCU1.20, TRRS1.R2
P3: MCU1.19, S26.1, S27.1, S28.1, S29.1
P4: MCU1.18, S22.1, S23.1, S24.1, S25.1
P5: MCU1.17, S17.1, S18.1, S19.1, S20.1, S21.1
P6: MCU1.16, S1.1, S2.1, S3.1, S4.1
P7: MCU1.15, S5.1, S6.1, S7.1, S8.1, S30.1
P8: MCU1.14, S9.1, S10.1, S11.1, S12.1, S31.1
P9: D17.1, D30.1, D31.1, D32.1, MCU1.13
P10: D3.1, D7.1, D11.1, D15.1, D20.1, D24.1, D28.1, MCU1.12
P14: D1.1, D5.1, D9.1, D13.1, D18.1, D22.1, D26.1, MCU1.10
P15: D4.1, D8.1, D12.1, D16.1, D21.1, D25.1, D29.1, MCU1.9
P16: D2.1, D6.1, D10.1, D14.1, D19.1, D23.1, D27.1, MCU1.11
P19: MCU1.7, S13.1, S14.1, S15.1, S16.1, S32.1
RST: B1.2, MCU1.3
VCC: MCU1.4, TRRS1.T
dash_home: D23.2, S23.2
dash_lower: D22.2, S22.2
dash_num: D25.2, S25.2
dash_upper: D24.2, S24.2
equal_home: D27.2, S27.2
equal_lower: D26.2, S26.2
equal_num: D29.2, S29.2
equal_upper: D28.2, S28.2
mirror_five_home: D14.2, S14.2
mirror_five_lower: D13.2, S13.2
mirror_five_mod: D32.2, S32.2
mirror_five_num: D16.2, S16.2
mirror_five_upper: D15.2, S15.2
mirror_four_home: D10.2, S10.2
mirror_four_lower: D9.2, S9.2
mirror_four_mod: D31.2, S31.2
mirror_four_num: D12.2, S12.2
mirror_four_upper: D11.2, S11.2
mirror_three_home: D6.2, S6.2
mirror_three_lower: D5.2, S5.2
mirror_three_mod: D30.2, S30.2
mirror_three_num: D8.2, S8.2
mirror_three_upper: D7.2, S7.2
mirror_two_home: D2.2, S2.2
mirror_two_lower: D1.2, S1.2
mirror_two_num: D4.2, S4.2
mirror_two_upper: D3.2, S3.2
zero_home: D19.2, S19.2
zero_lower: D18.2, S18.2
zero_mod: D17.2, S17.2
zero_num: D21.2, S21.2
zero_upper: D20.2, S20.2

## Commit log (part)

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2026-03-29 Restructure versions table, standardize MCU references with manufacturer links and chips
2026-03-29 Fix blank comment line in mcu_liatris header
2026-04-03 Add min-release-age=7 to .npmrc for supply chain security
2026-06-08 chore: add dependabot with 7-day cooldown
2026-06-13 Register custom footprints in Ergogen GUI image and harden Dockerfile
    Bump base image to node:24-alpine, pin ergogen-gui to v20251103 with a
    frozen lockfile, and run as the non-root node user (with a compose
    sysctl so it can still bind port 80). Register mcu_liatris, sod-123fl,
    and sod-123w in ergogen's footprint index with a grep guard so a failed
    registration breaks the build. Add .dockerignore to shrink the build
    context and document the GUI workflow in the README.
2026-06-13 Improve README clarity and cross-version consistency
    - Add design-pipeline overview to root README
    - Fix Kicad -> KiCad casing
    - Align v1/v2 section headings with other versions
    - Fix garbled v1 PCB offset explanation
2026-06-13 Label v4 TRRS protection parts descriptively
    TVS (sod-123fl): name pads K (cathode/'to') and A (anode/'from') instead
    of 1/2, set the value to SMF3.3CA, and document the params/pads in comments.
    Resistor (smd_0805): override designator to R (R1, not the generic SMD1)
    and add a '100R' silk value label. Document each part's pad->net mapping
    in the ergogen config comments.
2026-06-13 Sync v4 kicad working PCBs with finalized TRRS protection placement
2026-06-14 Add npm run autoroute for headless Freerouting
    Adds scripts/autoroute.py: per-board KiCad Specctra DSN export -> freerouting (headless via FREEROUTING__GUI__ENABLED=false) -> SES import, saved in place. The autoroute npm script loops over the wor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
2026-06-14 Remove .npmrc min-release-age (unsupported by installed npm)
2026-06-14 Sort v4 BOM rows; nudge data_resistor placement down 1mm
2026-06-14 Rename v4 matrix rows to symmetric scheme
    number->num, top->upper, bottom->lower, meta->mod (home unchanged),
    reading top-to-bottom around the home row. Updates all key definitions,
    rows declarations, thumbcluster keys, and derived point-name refs.
    No firmware impact: matrix coupling is via column_net/row_net, not
    row names.
2026-06-14 Wire npm scripts to bash files; add timestamped kicad backups
    Point the multi-step npm scripts at the executable scripts/*.sh wrappers and
    rename the copy scripts to name both endpoints (copy-pcbs-dist-to-kicad,
    copy-pcbs-kicad-to-routed, copy-traces-routed-to-kicad) so their direction is
    unambiguous. copy-pcbs-dist-to-kicad now backs up each existing kicad PCB to
    kicad/backups/<name>-<timestamp>.kicad_pcb before overwriting, so routing work
    is recoverable; gitignore that dir. Update README and inline references.
2026-06-14 Fix v4 silk credit mirroring: center-justify so back copy stays on-board
    Left/right-justified reversible text mirrors about its anchor, so the
    B.SilkS copy landed off the board edge (verified via pcbnew bbox: left
    back copy at x[86.8,132.4], board starts at 130.8). Switch the credit
    text to center justification (drop align) so the mirrored back copy lands
    on the same on-board region as the front. Anchor x (credit_x_left/right
    units) centers the ~45.6mm URL ~1.5mm inside each pinky edge.
2026-06-15 Enlarge v4 component silk to 0.8mm; drop resistor to make room
    Bump the TVS, resistor and screw labels to 0.8mm (fab-safe min, uniform
    with the other component labels) and move parts to fit:
    - TVS label fits in-channel at 0.8, so the TVS stays at the R2 data pad
    (clamp placement preserved).
    - The resistor's part number (ERJ-6ENF1000V, ~10mm at 0.8) is too wide for
    the MCU-to-edge channel, so the resistor is dropped beside the MCU's lower
2026-06-15 Add brands/part numbers to v4 reset, resistor, TVS silk labels
    - reset: 'RESET' -> 'Reset switch / E-Switch / TL3342F450QG'
    - resistor: add 'Panasonic' line -> '100R / Panasonic / ERJ-6ENF / 1000V'
    - TVS: add 'Littelfuse' line -> 'TVS / Littelfuse / SMF3.3CA'
    - Fix two stale right-half label shifts (TVS, reset) that hadn't been
    updated when the left ones moved, which put the right TVS label over the
    TVS footprint.
2026-06-15 Tighten v4 config comments
    Condense the verbose multi-line and trailing comments throughout (origin,
    mirror/source-of-truth, extra/screw zones, outline geometry, binding, TRRS/
    TVS/resistor headers, MCU side-flip, label/credit blocks, unit notes) while
    keeping the essential numbers and non-obvious rationale. Comments only.
2026-06-15 Regenerate v4 PCBs and add routed masters with GND pour
    Regenerate left/right working boards from the updated ergogen config and add the
    v4/kicad/routed/ masters (the fab source), each carrying the B.Cu GND pour added
    by copy-pcbs-kicad-to-routed.
2026-06-15 v4 docs: add Fabrication section; error on empty lcsc
    - README: add JLCPCB Fabrication section (export flow, part-assignment
    rules, ordering steps with zip/BOM/CPL paths and DFM viewer link);
    drop the Part dimensions section
    - gen-jlcpcb-bom-cpl.py: a listed footprint with empty lcsc is now a
    hard error (exit 1, nothing written) instead of a skipped warning
    - jlcpcb-parts.json: update _comment to match the error behavior
2026-06-15 v4: add component silkscreen labels
    Single-sided labels placed on each part's mount side: MCU and TRRS on
    the front, all SMD parts (diodes, resistor, TVS, reset switch) on the
    back (mirrored so they read from the back). Adds reset GND/RST pad
    labels and a diode + hotswap-socket part-number label in each half's
    bottom-pinky margin.
2026-06-15 v4: parameterize thumb diode offset, center under switch
    Add thumb_diode_dy/dx units for the horizontal thumb diodes' offset from
    their splayed switches. dx re-centers laterally (the rotated dy would drift
    it sideways); keep dx = dy * tan(thumb_splay) so it stays centered when dy
    changes, and dx auto-flips x on the mirrored right half. Set dy to -4.7
    (sits ~4.97mm below the switch, level with the matrix diodes), centered.
    Regenerate both halves and the routed copies.
2026-06-15 v4: rework right-half matrix nets
    Remap the right half's column and row nets so the mirrored matrix and
    extra inner columns route off a different MCU bank: columns five..two ->
    P19,P8,P7,P6 plus P5,P4,P3 for the extra inner columns; rows mod/lower/
    home/upper/num -> P9/P14/P16/P10/P15. P2 (GP2) stays free for the TRRS
    serial pin; P0 (GP1), P18 (GP26), and P20 (GP28) are now unused on the
    right. Regenerate the unrouted boards; manual re-route still pending.
2026-06-16 v4: re-sync unrouted boards (rebuild + traces + provenance stamp)
    Regenerate the unrouted working boards from the current config, copy the
    human routing back in from the routed masters, and carry the refreshed
    provenance stamp.
2026-06-16 README: drop host-specific /opt/kikit venv from panelize requirement
2026-06-16 v4: re-sync routed + unrouted boards (rebuild + traces + provenance stamp)
2026-06-16 v4: reassign left-half matrix pins, re-sync boards, harden GND guard
    config.yaml: column five left -> P15 (was P10) and swap the lower/home/
    upper row_net assignments (P14/P16/P10). Re-sync routed/ + unrouted/
    left and right boards to the new config.
    add-gnd-zone.py: exclude teardrop zones from the already-poured guard (a
    teardrop on a GND track is itself a GND zone, which made the guard see a
    pour that was never flooded and skip the real fill); clearer
2026-06-16 validate-fab: gate on teardrop consistency between routed halves
    The mirrored left/right masters should carry comparable teardrop counts,
    but the trace-copy workflow drops teardrops on a re-routed half, so one
    half can silently lose them. The first v4 JLCPCB order shipped this way
    (459 teardrops left vs 14 right); every existing gate passed because
    teardrops are non-functional and DRC stays clean.
    Add check 6: collect teardrop-zone counts per board, then fail any board
2026-06-16 v4: fabrication build (ordering this from JLCPCB)
    Validated fab-ready and sent to JLCPCB. Teardrops symmetric (459 left /
    496 right zones), GND pour filled on B.Cu (~13000mm^2 master, ~157x118mm
    flood in the shipped B_Cu gerber), DRC clean (0 violations / 0 unconnected
    both halves), provenance matches config, gerber set + assembly complete.
    Provenance stamp (routed masters):
    splinter v=v4 built=2026-06-16T16:30:02Z config=f66b61addc4d commit=d2fd01a clean=yes
2026-06-19 v4: fillet switch cutouts for CNC, enlarge to 14.5mm, export both curve sets
    Add a 1mm internal corner radius (cnc_fillet unit) to the switch cutouts so
    a 2mm CNC end mill can cut them, and enlarge the cutout (c 14 -> 14.5) to
    clear that round: a Cherry MX housing fits a 14.0mm/0.3mm-corner cutout, so
    the sharp-corner-equivalent boss is ~13.82mm, needing ~14.41mm min for a 1mm
    fillet; 14.5 adds margin (verified by test print). 1mm is JLCCNC's
    price-friendly floor (sturdy 2mm tool; 0.5mm needs a costlier micro mill).
2026-06-20 v4: add Onshape v4.5 case model STEP export
2026-06-21 v4: document socketed MCU, GP19 VBUS pin, and TVS turn-on voltage in README
2026-06-21 v4: add TRRS pad-net silk labels (GND/DATA/VCC) down the jack centerline
    Reuses the side-B mirrored label_params (like the reset GND/RST pad labels).
    Each label sits in the centerline gap between the symmetric jack's two pad
    columns, level with its net's pad row. Mirrored to the right half via
    mirror_matrix_five_num.
2026-06-22 v4: re-stamp boards clean=yes from committed source (06c8ffa)
    Full pipeline rebuild on the now-committed tree: routed + unrouted boards
    carry clean=yes commit=06c8ffa, so the provenance stamp is authoritative.
    config unchanged (9096bb80de4e). All gates pass: connectivity DRC clean,
    GND flood present (master + gerber), full gerber set, BOM/CPL complete,
    teardrops 277 left / 295 right. validate:fab passes with zero warnings.
2026-06-23 v4: thumb geometry y-gap ~1.0 + smaller thumb_inner_pad; robust keepout edge reading
    - config: re-solve to y-gap ~0.96 / X-gap 0.74 (splay -19.20, thumb_inner_pad 0.9
    splayed inner-edge polygon, thumb-bottom 0.69), keepout-clean both halves;
    clean up the thumb comments.
    - add-keepout-zones: move near-zero-length Edge.Cuts shapes off-layer (SetLayer,
    not board.Remove which corrupts pcbnew's SWIG state) so an exact-coincidence
    corner no longer crashes GetBoardPolygonOutlines.

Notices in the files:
README.md:
License: MIT
